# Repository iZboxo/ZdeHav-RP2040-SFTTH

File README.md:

# ZdeHav-RP2040-SFTTH
Stepper, fan, thermistor, thermistor and heater. Does it work? I don't know yet. But I hope so.

# What I know is wrong even now lol
BAV99W - has different mounting pads - one is meant for hand soldering, one for machine. Not a hard issue.
SK310A-TP D3, D4 - also different mounting style, this IS BAD. I missed this one. I only found 40V/0.3A schottky in 0603 - AND THATS NOT ENOUGH.

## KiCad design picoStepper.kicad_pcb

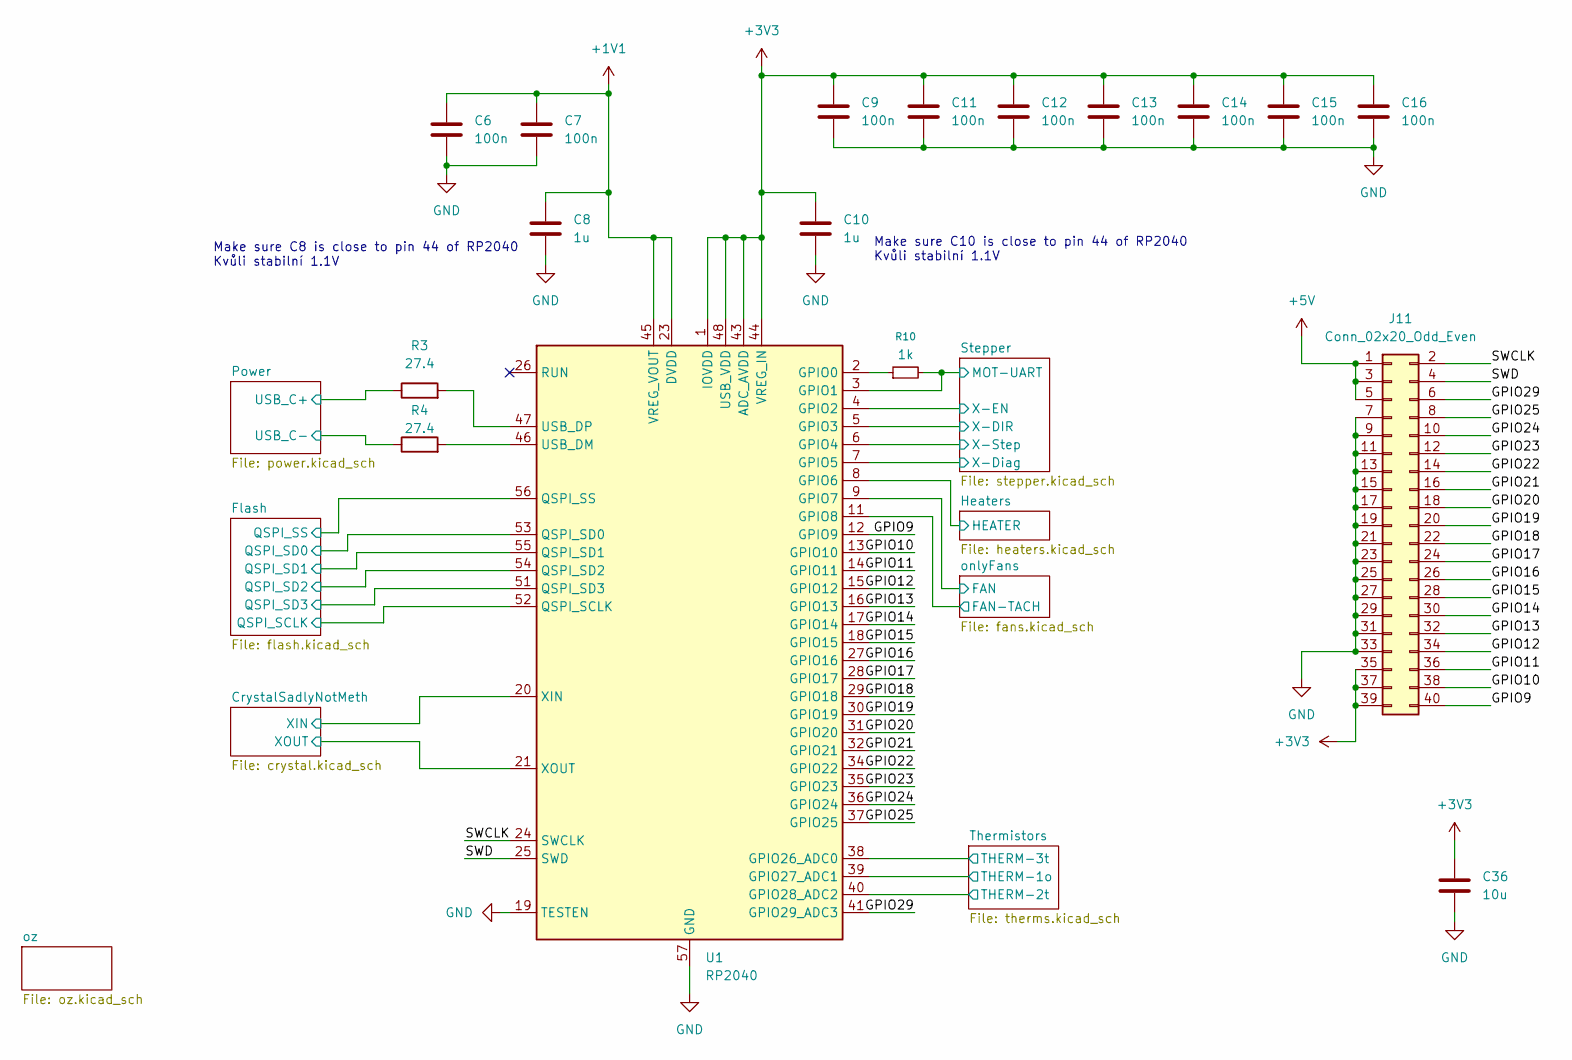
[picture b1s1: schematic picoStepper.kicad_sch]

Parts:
C6, C7, C9, C11, C12, C13, C14, C15, C16: 100n; C_0603_1608Metric_Pad1.08x0.95mm_HandSolder
C8, C10: 1u; C_0603_1608Metric_Pad1.08x0.95mm_HandSolder
C36: 10u; C_0805_2012Metric_Pad1.18x1.45mm_HandSolder
J11: Conn_02x20_Odd_Even; PinSocket_2x20_P2.54mm_Vertical
R3, R4: 27.4; R_0603_1608Metric_Pad0.98x0.95mm_HandSolder
R10: 1k; R_0603_1608Metric_Pad0.98x0.95mm_HandSolder
U1: RP2040; QFN-56-1EP_7x7mm_P0.4mm_EP3.2x3.2mm

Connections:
+1V1: C6.1, C7.1, C8.1, U1.23 (DVDD), U1.45 (VREG_VOUT), U1.50 (DVDD)
+3V3: C9.1, C10.1, C11.1, C12.1, C13.1, C14.1, C15.1, C16.1, C36.1, J11.35, J11.37, J11.39, U1.1 (IOVDD), U1.10 (IOVDD), U1.22 (IOVDD), U1.33 (IOVDD), U1.42 (IOVDD), U1.43 (ADC_AVDD), U1.44 (VREG_IN), U1.48 (USB_VDD), U1.49 (IOVDD); also elsewhere on the board
+5V: J11.1, J11.3, J11.5; also elsewhere on the board
/CrystalSadlyNotMeth/XIN: U1.20 (XIN); also elsewhere on the board
/CrystalSadlyNotMeth/XOUT: U1.21 (XOUT); also elsewhere on the board
/Flash/QSPI_SCLK: U1.52 (QSPI_SCLK); also elsewhere on the board
/Flash/QSPI_SD0: U1.53 (QSPI_SD0); also elsewhere on the board
/Flash/QSPI_SD1: U1.55 (QSPI_SD1); also elsewhere on the board
/Flash/QSPI_SD2: U1.54 (QSPI_SD2); also elsewhere on the board
/Flash/QSPI_SD3: U1.51 (QSPI_SD3); also elsewhere on the board
/Flash/QSPI_SS: U1.56 (QSPI_SS); also elsewhere on the board
/GPIO9: J11.40, U1.12 (GPIO9)
/GPIO10: J11.38, U1.13 (GPIO10)
/GPIO11: J11.36, U1.14 (GPIO11)
/GPIO12: J11.34, U1.15 (GPIO12)
/GPIO13: J11.32, U1.16 (GPIO13)
/GPIO14: J11.30, U1.17 (GPIO14)
/GPIO15: J11.28, U1.18 (GPIO15)
/GPIO16: J11.26, U1.27 (GPIO16)
/GPIO17: J11.24, U1.28 (GPIO17)
/GPIO18: J11.22, U1.29 (GPIO18)
/GPIO19: J11.20, U1.30 (GPIO19)
/GPIO20: J11.18, U1.31 (GPIO20)
/GPIO21: J11.16, U1.32 (GPIO21)
/GPIO22: J11.14, U1.34 (GPIO22)
/GPIO23: J11.12, U1.35 (GPIO23)
/GPIO24: J11.10, U1.36 (GPIO24)
/GPIO25: J11.8, U1.37 (GPIO25)
/GPIO29: J11.6, U1.41 (GPIO29_ADC3)
/Heaters/HEATER: U1.8 (GPIO6); also elsewhere on the board
/Power/USB_C+: R3.1; also elsewhere on the board
/Power/USB_C-: R4.1; also elsewhere on the board
/SWCLK: J11.2, U1.24 (SWCLK)
/SWD: J11.4, U1.25 (SWD)
/Stepper/MOT-UART: R10.2, U1.3 (GPIO1); also elsewhere on the board
/Stepper/X-DIR: U1.5 (GPIO3); also elsewhere on the board
/Stepper/X-Diag: U1.7 (GPIO5); also elsewhere on the board
/Stepper/X-EN: U1.4 (GPIO2); also elsewhere on the board
/Stepper/X-Step: U1.6 (GPIO4); also elsewhere on the board
/Thermistors/THERM-1o: U1.39 (GPIO27_ADC1); also elsewhere on the board
/Thermistors/THERM-2t: U1.40 (GPIO28_ADC2); also elsewhere on the board
/Thermistors/THERM-3t: U1.38 (GPIO26_ADC0); also elsewhere on the board
/onlyFans/FAN: U1.9 (GPIO7); also elsewhere on the board
/onlyFans/FAN-TACH: U1.11 (GPIO8); also elsewhere on the board
GND: C6.2, C7.2, C8.2, C9.2, C10.2, C11.2, C12.2, C13.2, C14.2, C15.2, C16.2, C36.2, J11.7, J11.9, J11.11, J11.13, J11.15, J11.17, J11.19, J11.21, J11.23, J11.25, J11.27, J11.29, J11.31, J11.33, U1.19 (TESTEN), U1.57 (GND); also elsewhere on the board
unnamed: R10.1, U1.2 (GPIO0)
unnamed: R4.2, U1.46 (USB_DM)
unnamed: R3.2, U1.47 (USB_DP)

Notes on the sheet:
Make sure C10 is close to pin 44 of RP2040 Kvůli stabilní 1.1V
Make sure C8 is close to pin 44 of RP2040 Kvůli stabilní 1.1V

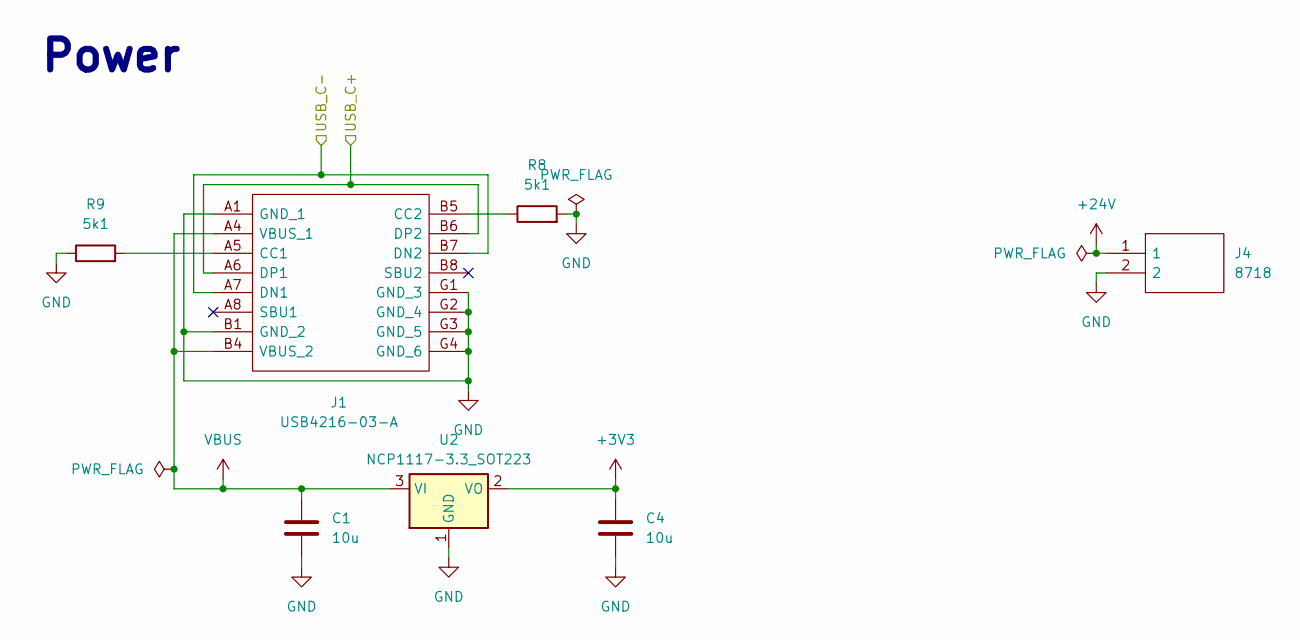
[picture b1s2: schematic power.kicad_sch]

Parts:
C1, C4: 10u; C_0805_2012Metric_Pad1.18x1.45mm_HandSolder
J1: USB4216-03-A; USB421603A; Mouser Part Number 640-USB4216-03-A
J4: 8718; SHDR2W99P0X500_1X2_1001X762X1001P; Mouser Part Number 534-8718
R8, R9: 5k1; R_0603_1608Metric_Pad0.98x0.95mm_HandSolder
U2: NCP1117-3.3_SOT223; SOT-223-3_TabPin2

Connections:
+3V3: C4.1, U2.2 (VO); also elsewhere on the board
+24V: J4.1; also elsewhere on the board
/Power/USB_C+: J1.A6 (DP1), J1.B6 (DP2); also elsewhere on the board
/Power/USB_C-: J1.A7 (DN1), J1.B7 (DN2); also elsewhere on the board
GND: C1.2, C4.2, J1.A1 (GND_1), J1.B1 (GND_2), J1.G1 (GND_3), J1.G2 (GND_4), J1.G3 (GND_5), J1.G4 (GND_6), J4.2, R8.2, R9.1, U2.1 (GND); also elsewhere on the board
unnamed: J1.A5 (CC1), R9.2
unnamed: J1.B5 (CC2), R8.1
VBUS: C1.1, J1.A4 (VBUS_1), J1.B4 (VBUS_2), U2.3 (VI)

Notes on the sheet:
Power

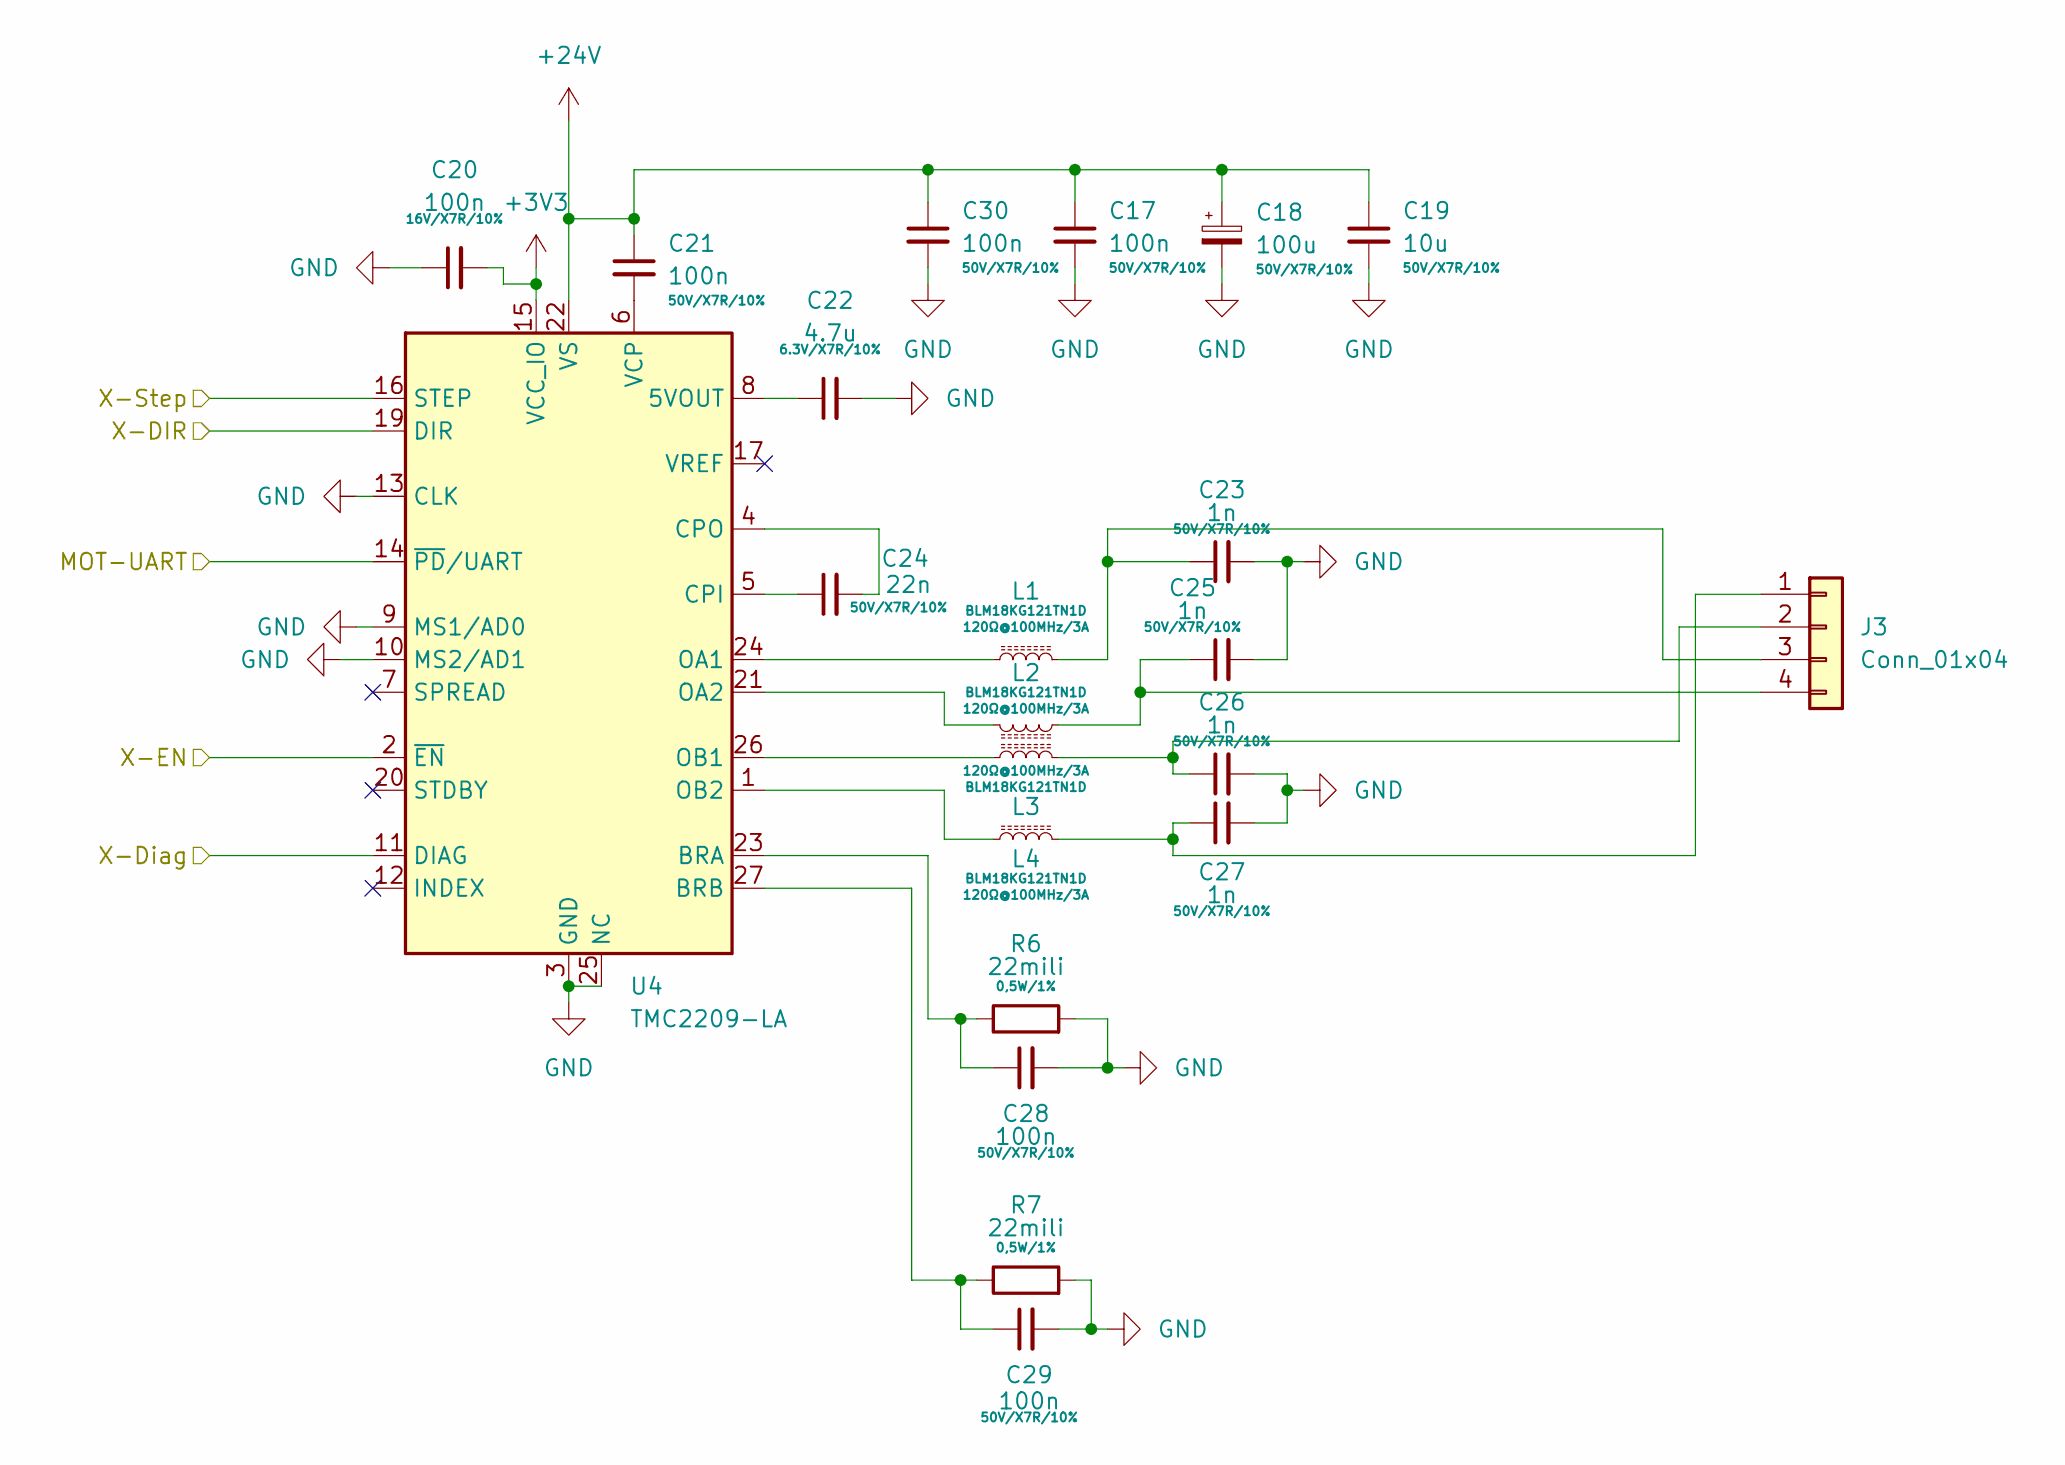
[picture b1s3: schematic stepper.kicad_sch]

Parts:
C17, C20, C21, C28, C29, C30: 100n; C_0603_1608Metric_Pad1.08x0.95mm_HandSolder
C18: 100u; CAPAE830X1050N
C19: 10u; C_1206_3216Metric_Pad1.33x1.80mm_HandSolder
C22: 4.7u; C_0603_1608Metric_Pad1.08x0.95mm_HandSolder
C23, C25, C26, C27: 1n; C_0603_1608Metric_Pad1.08x0.95mm_HandSolder
C24: 22n; C_0603_1608Metric_Pad1.08x0.95mm_HandSolder
J3: Conn_01x04; SHDR4W97P0X254_1X4_1271X660X1143P
L1, L2, L3, L4: BLM18KG121TN1D; D_0603_1608Metric_Pad1.05x0.95mm_HandSolder
R6, R7: 22mili; R_1206_3216Metric_Pad1.30x1.75mm_HandSolder
U4: TMC2209-LA; VQFN-28-1EP_5x5mm_P0.5mm_EP3.7x3.7mm_ThermalVias

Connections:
+3V3: C20.2, U4.15 (VCC_IO); also elsewhere on the board
+24V: C17.1, C18.1, C19.1, C21.1, C30.1, U4.22 (VS), U4.28 (VS); also elsewhere on the board
/Stepper/MOT-UART: U4.14 (~PD/UART); also elsewhere on the board
/Stepper/X-DIR: U4.19 (DIR); also elsewhere on the board
/Stepper/X-Diag: U4.11 (DIAG); also elsewhere on the board
/Stepper/X-EN: U4.2 (~EN); also elsewhere on the board
/Stepper/X-Step: U4.16 (STEP); also elsewhere on the board
GND: C17.2, C18.2, C19.2, C20.1, C22.2, C23.2, C25.2, C26.2, C27.2, C28.2, C29.2, C30.2, R6.2, R7.2, U4.3 (GND), U4.9 (MS1/AD0), U4.10 (MS2/AD1), U4.13 (CLK), U4.18 (GND), U4.25 (NC), U4.29 (GND); also elsewhere on the board
unnamed: C27.1, J3.1, L4.2
unnamed: C26.1, J3.2, L3.2
unnamed: C23.1, J3.3, L1.2
unnamed: C25.1, J3.4, L2.1
unnamed: C22.1, U4.8 (5VOUT)
unnamed: C28.1, R6.1, U4.23 (BRA)
unnamed: C29.1, R7.1, U4.27 (BRB)
unnamed: C24.1, U4.5 (CPI)
unnamed: C24.2, U4.4 (CPO)
unnamed: L1.1, U4.24 (OA1)
unnamed: L2.2, U4.21 (OA2)
unnamed: L3.1, U4.26 (OB1)
unnamed: L4.1, U4.1 (OB2)
unnamed: C21.2, U4.6 (VCP)

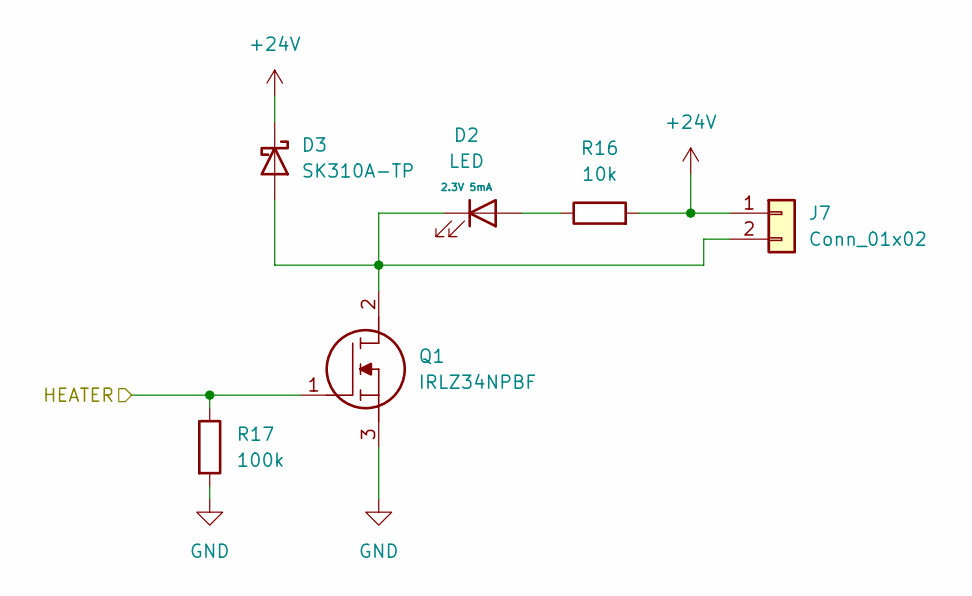
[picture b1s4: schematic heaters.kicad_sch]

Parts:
D2: LED; D_0603_1608Metric_Pad1.05x0.95mm_HandSolder
D3: SK310A-TP; D_0603_1608Metric_Pad1.05x0.95mm_HandSolder
J7: Conn_01x02; SHDR2W99P0X500_1X2_1001X762X1001P
Q1: IRLZ34NPBF; TO-220-3_Horizontal_TabDown; Mouser Part Number 942-IRLZ34NPBF
R16: 10k; R_0603_1608Metric_Pad0.98x0.95mm_HandSolder
R17: 100k; R_0603_1608Metric_Pad0.98x0.95mm_HandSolder

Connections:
+24V: D3.1 (K), J7.1, R16.2; also elsewhere on the board
/Heaters/HEATER: Q1.1, R17.1; also elsewhere on the board
GND: Q1.3, R17.2; also elsewhere on the board
unnamed: D2.2 (A), R16.1
unnamed: D2.1 (K), D3.2 (A), J7.2, Q1.2

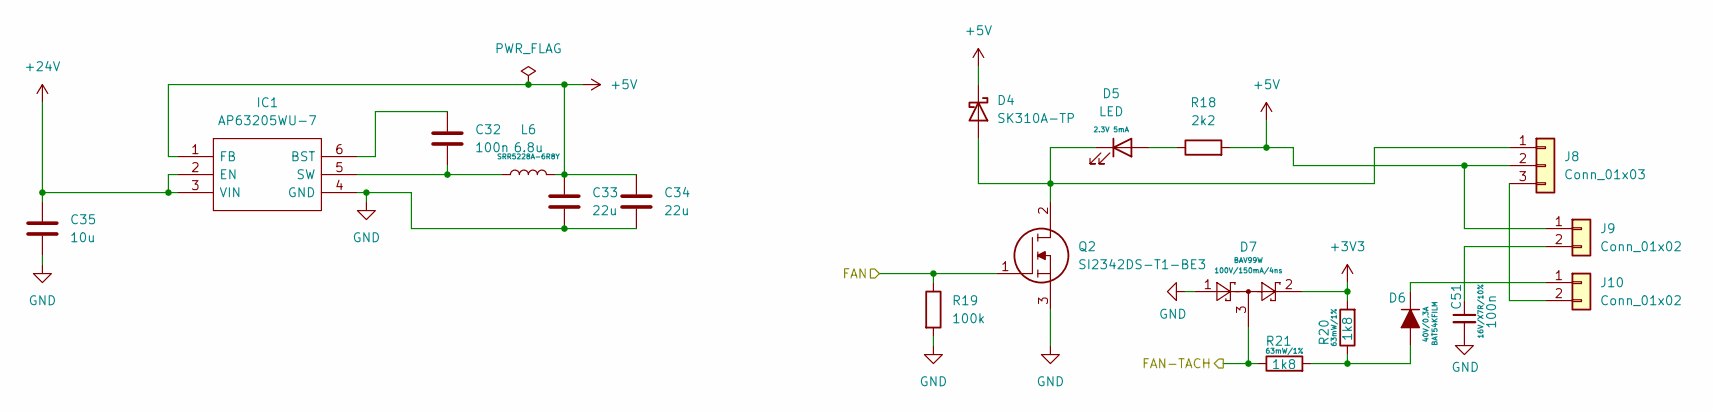
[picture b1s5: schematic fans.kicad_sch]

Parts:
C32, C51: 100n; C_0603_1608Metric_Pad1.08x0.95mm_HandSolder
C33, C34: 22u; C_0603_1608Metric_Pad1.08x0.95mm_HandSolder
C35: 10u; C_0603_1608Metric_Pad1.08x0.95mm_HandSolder
D4: SK310A-TP; D_0603_1608Metric_Pad1.05x0.95mm_HandSolder
D5: LED; D_0603_1608Metric_Pad1.05x0.95mm_HandSolder
D6: BAT54KFILM; D_SOD-523
D7: BAV99W; SOT-323_SC-70
IC1: AP63205WU-7; AP63205WU7; Mouser Part Number 621-AP63205WU-7
J8: Conn_01x03; RHDR3W64P0X254_1X3_1017X660X1194P
J9, J10: Conn_01x02; PinHeader_1x02_P2.54mm_Vertical
L6: 6.8u; L_APV_APH0530
Q2: SI2342DS-T1-BE3; SOT-23-3; Mouser Part Number 942-IRLZ34NPBF
R18: 2k2; R_0603_1608Metric_Pad0.98x0.95mm_HandSolder
R19: 100k; R_0603_1608Metric_Pad0.98x0.95mm_HandSolder
R20, R21: 1k8; R_0603_1608Metric_Pad0.98x0.95mm_HandSolder

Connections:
+3V3: D7.2, R20.2; also elsewhere on the board
+5V: C33.1, C34.1, D4.1 (K), IC1.1 (FB), J8.2, J9.1, L6.2, R18.2; also elsewhere on the board
+24V: C35.1, IC1.2 (EN), IC1.3 (VIN); also elsewhere on the board
/onlyFans/FAN: Q2.1, R19.1; also elsewhere on the board
/onlyFans/FAN-TACH: D7.3, R21.1; also elsewhere on the board
GND: C33.2, C34.2, C35.2, C51.2, D7.1, IC1.4 (GND), Q2.3, R19.2; also elsewhere on the board
unnamed: D4.2 (A), D5.1 (K), J8.1, Q2.2
unnamed: D5.2 (A), R18.1
unnamed: D6.2 (A), R20.1, R21.2
unnamed: D6.1 (K), J10.1
unnamed: C32.1, IC1.6 (BST)
unnamed: C32.2, IC1.5 (SW), L6.1
unnamed: C51.1, J9.2
unnamed: J8.3, J10.2

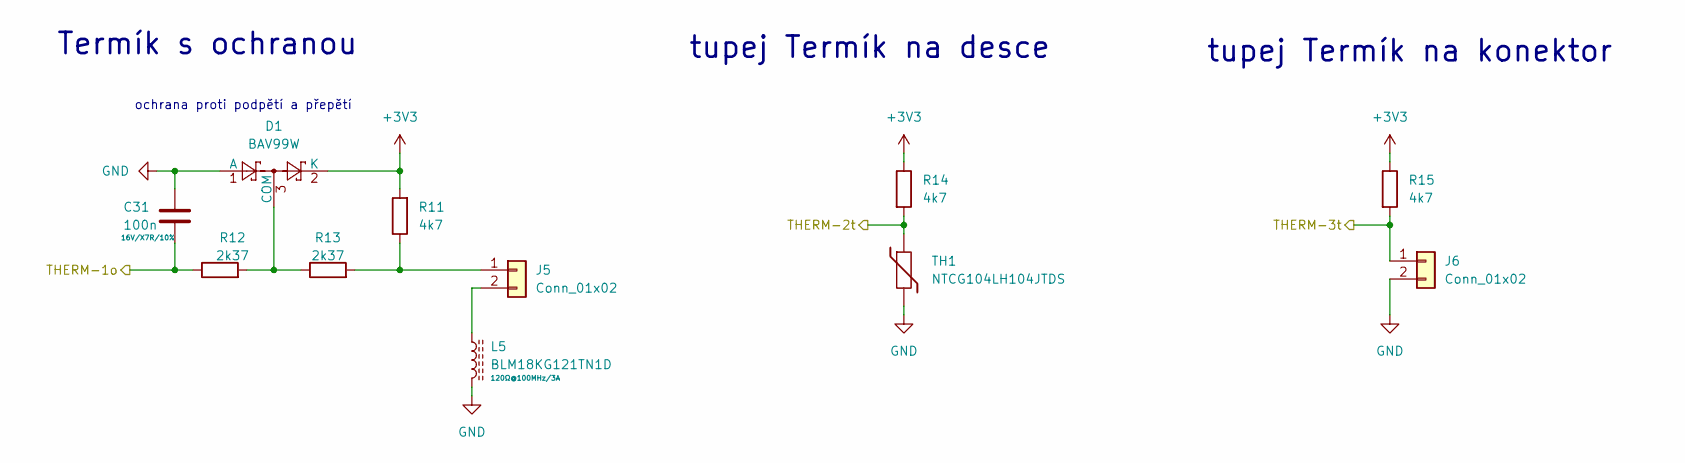
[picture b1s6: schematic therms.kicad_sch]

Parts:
C31: 100n; C_0603_1608Metric_Pad1.08x0.95mm_HandSolder
D1: BAV99W; SOT-323_SC-70_Handsoldering
J5, J6: Conn_01x02; SHDR2W64P0X254_1X2_737X660X1181P
L5: BLM18KG121TN1D; D_0603_1608Metric_Pad1.05x0.95mm_HandSolder
R11, R14, R15: 4k7; R_0603_1608Metric_Pad0.98x0.95mm_HandSolder
R12, R13: 2k37; R_0603_1608Metric_Pad0.98x0.95mm_HandSolder
TH1: NTCG104LH104JTDS; R_0402_1005Metric_Pad0.72x0.64mm_HandSolder

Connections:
+3V3: D1.2 (K), R11.2, R14.1, R15.1; also elsewhere on the board
/Thermistors/THERM-1o: C31.2, R12.1; also elsewhere on the board
/Thermistors/THERM-2t: R14.2, TH1.1; also elsewhere on the board
/Thermistors/THERM-3t: J6.1, R15.2; also elsewhere on the board
GND: C31.1, D1.1 (A), J6.2, L5.2, TH1.2; also elsewhere on the board
unnamed: D1.3 (COM), R12.2, R13.1
unnamed: J5.1, R11.1, R13.2
unnamed: J5.2, L5.1

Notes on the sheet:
ochrana proti podpětí a přepětí
tupej Termík na konektor
Termík s ochranou
tupej Termík na desce

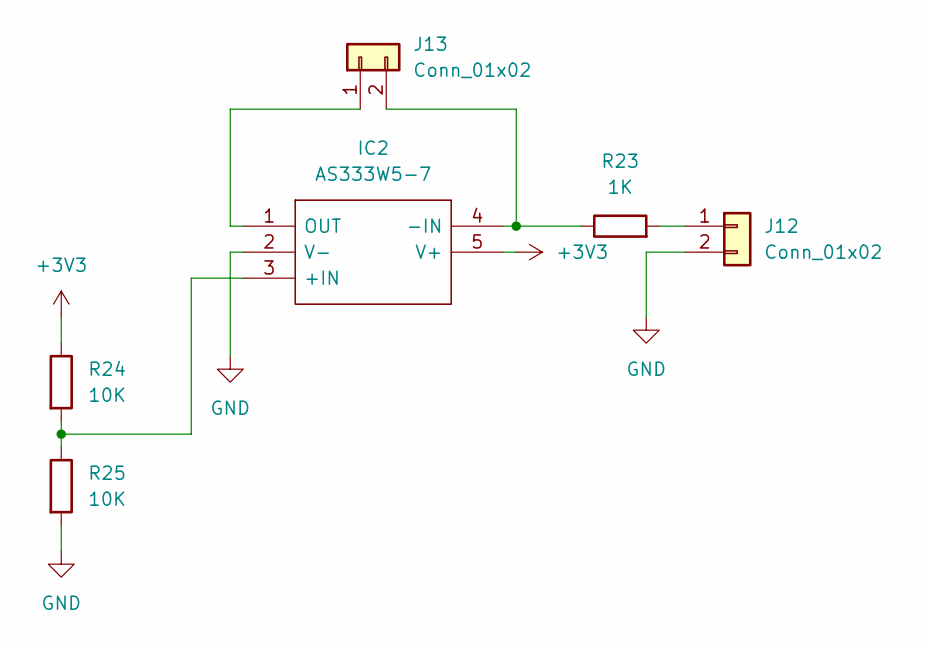
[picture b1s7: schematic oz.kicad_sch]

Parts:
IC2: AS333W5-7; SOT95P285X140-5N; Mouser Part Number 621-AS333W5-7
J12, J13: Conn_01x02; PinHeader_1x02_P2.54mm_Vertical
R23: 1K; R_0603_1608Metric_Pad0.98x0.95mm_HandSolder
R24, R25: 10K; R_0603_1608Metric_Pad0.98x0.95mm_HandSolder

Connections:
unnamed: IC2.1 (OUT), J13.1
unnamed: IC2.2 (V-), J12.2, R25.2
unnamed: IC2.3 (+IN), R24.2, R25.1
unnamed: IC2.4 (-IN), J13.2, R23.1
unnamed: IC2.5 (V+), R24.1
unnamed: J12.1, R23.2

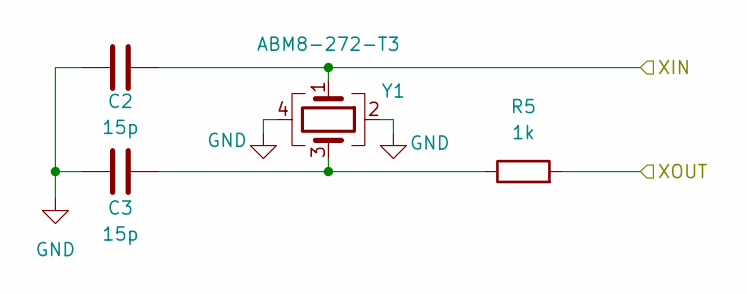
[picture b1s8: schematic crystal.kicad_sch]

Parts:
C2, C3: 15p; C_0603_1608Metric_Pad1.08x0.95mm_HandSolder
R5: 1k; R_0603_1608Metric_Pad0.98x0.95mm_HandSolder
Y1: ABM8-272-T3; Crystal_SMD_Abracon_ABM8G-4Pin_3.2x2.5mm

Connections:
/CrystalSadlyNotMeth/XIN: C2.2, Y1.1; also elsewhere on the board
/CrystalSadlyNotMeth/XOUT: R5.2; also elsewhere on the board
GND: C2.1, C3.1, Y1.2, Y1.4; also elsewhere on the board
unnamed: C3.2, R5.1, Y1.3

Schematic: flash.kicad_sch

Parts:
C5: C; C_0603_1608Metric_Pad1.08x0.95mm_HandSolder
J2: Conn_01x02; PinHeader_1x02_P2.54mm_Vertical
R1: 1k; R_0603_1608Metric_Pad0.98x0.95mm_HandSolder
R2: DNF; R_0603_1608Metric_Pad0.98x0.95mm_HandSolder
U3: W25Q128JVS; SOIC-8_5.3x5.3mm_P1.27mm

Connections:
+3V3: C5.1, R2.1, U3.8 (VCC); also elsewhere on the board
/Flash/QSPI_SCLK: U3.6 (CLK); also elsewhere on the board
/Flash/QSPI_SD0: U3.5 (DI/IO_{0}); also elsewhere on the board
/Flash/QSPI_SD1: U3.2 (DO/IO_{1}); also elsewhere on the board
/Flash/QSPI_SD2: U3.3 (~WP/IO_{2}); also elsewhere on the board
/Flash/QSPI_SD3: U3.7 (~HOLD/~RESET/IO_{3}); also elsewhere on the board
/Flash/QSPI_SS: R1.2, R2.2, U3.1 (~CS); also elsewhere on the board
GND: C5.2, J2.1, U3.4 (GND); also elsewhere on the board
unnamed: J2.2, R1.1

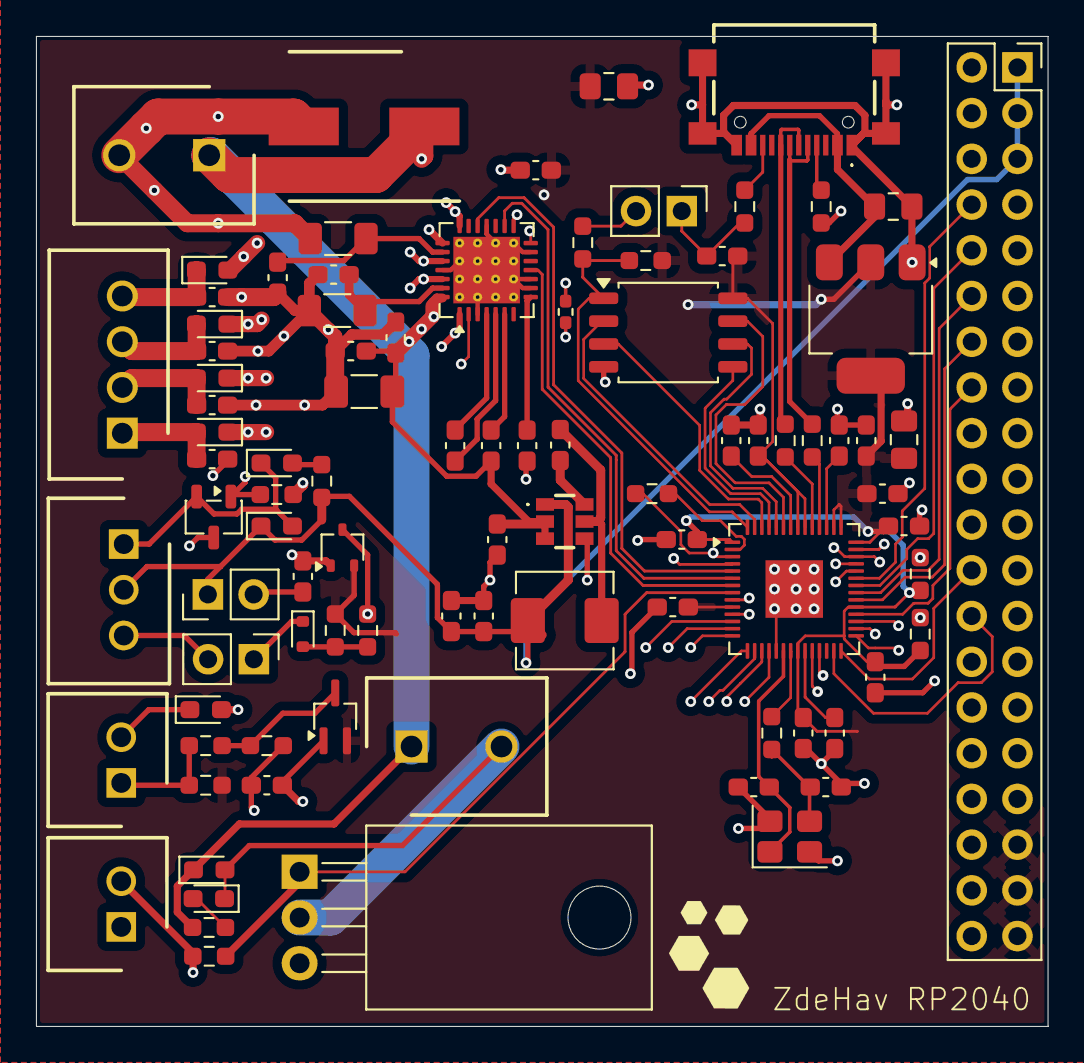
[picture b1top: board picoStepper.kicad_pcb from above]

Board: 4 copper layers, 56.2 x 55.0 mm, 91 parts (0 on the bottom side), 81 nets.

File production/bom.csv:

Designator,Footprint,Quantity,Value,LCSC Part #
"C1, C36, C4",0805,3,10u,
"C10, C8",0603,2,1u,
"C11, C12, C13, C14, C15, C16, C17, C20, C21, C28, C29, C30, C31, C32, C51, C6, C7, C9",0603,18,100n,
C18,CAPAE830X1050N,1,100u,
C19,1206,1,10u,
"C2, C3",0603,2,15p,
C22,0603,1,4.7u,
"C23, C25, C26, C27",0603,4,1n,
C24,0603,1,22n,
"C33, C34",0603,2,22u,
C35,0603,1,10u,
C5,0603,1,C,
D1,SOT-323_SC-70_Handsoldering,1,BAV99W,
"D2, D5",0603,2,LED,
"D3, D4",0603,2,SK310A-TP,
D6,D_SOD-523,1,BAT54KFILM,
D7,SOT-323_SC-70,1,BAV99W,
IC1,AP63205WU7,1,AP63205WU-7,
J1,USB421603A,1,USB4216-03-A,
"J10, J2, J9",PinHeader_1x02_P2.54mm_Vertical,3,Conn_01x02,
J11,PinSocket_2x20_P2.54mm_Vertical,1,Conn_02x20_Odd_Even,
J3,SHDR4W97P0X254_1X4_1271X660X1143P,1,Conn_01x04,
J4,SHDR2W99P0X500_1X2_1001X762X1001P,1,8718,
"J5, J6",SHDR2W64P0X254_1X2_737X660X1181P,2,Conn_01x02,
J7,SHDR2W99P0X500_1X2_1001X762X1001P,1,Conn_01x02,
J8,RHDR3W64P0X254_1X3_1017X660X1194P,1,Conn_01x03,
"L1, L2, L3, L4, L5",0603,5,BLM18KG121TN1D,
L6,L_APV_APH0530,1,6.8u,
Q1,TO-220-3_Horizontal_TabDown,1,IRLZ34NPBF,
Q2,SOT-23-3,1,SI2342DS-T1-BE3,
"R1, R10, R5",0603,3,1k,
"R11, R14, R15",0603,3,4k7,
"R12, R13",0603,2,2k37,
R16,0603,1,10k,
"R17, R19",0603,2,100k,
R18,0603,1,2k2,
R2,0603,1,DNF,
"R20, R21",0603,2,1k8,
"R3, R4",0603,2,27.4,
"R6, R7",1206,2,22mili,
"R8, R9",0603,2,5k1,
TH1,0402,1,NTCG104LH104JTDS,
U1,QFN-56-1EP_7x7mm_P0.4mm_EP3.2x3.2mm,1,RP2040,
U2,SOT-223-3_TabPin2,1,NCP1117-3.3_SOT223,
U3,SOIC-8_5.3x5.3mm_P1.27mm,1,W25Q128JVS,
U4,VQFN-28-1EP_5x5mm_P0.5mm_EP3.7x3.7mm_ThermalVias,1,TMC2209-LA,
Y1,Crystal_SMD_Abracon_ABM8G-4Pin_3.2x2.5mm,1,ABM8-272-T3,
